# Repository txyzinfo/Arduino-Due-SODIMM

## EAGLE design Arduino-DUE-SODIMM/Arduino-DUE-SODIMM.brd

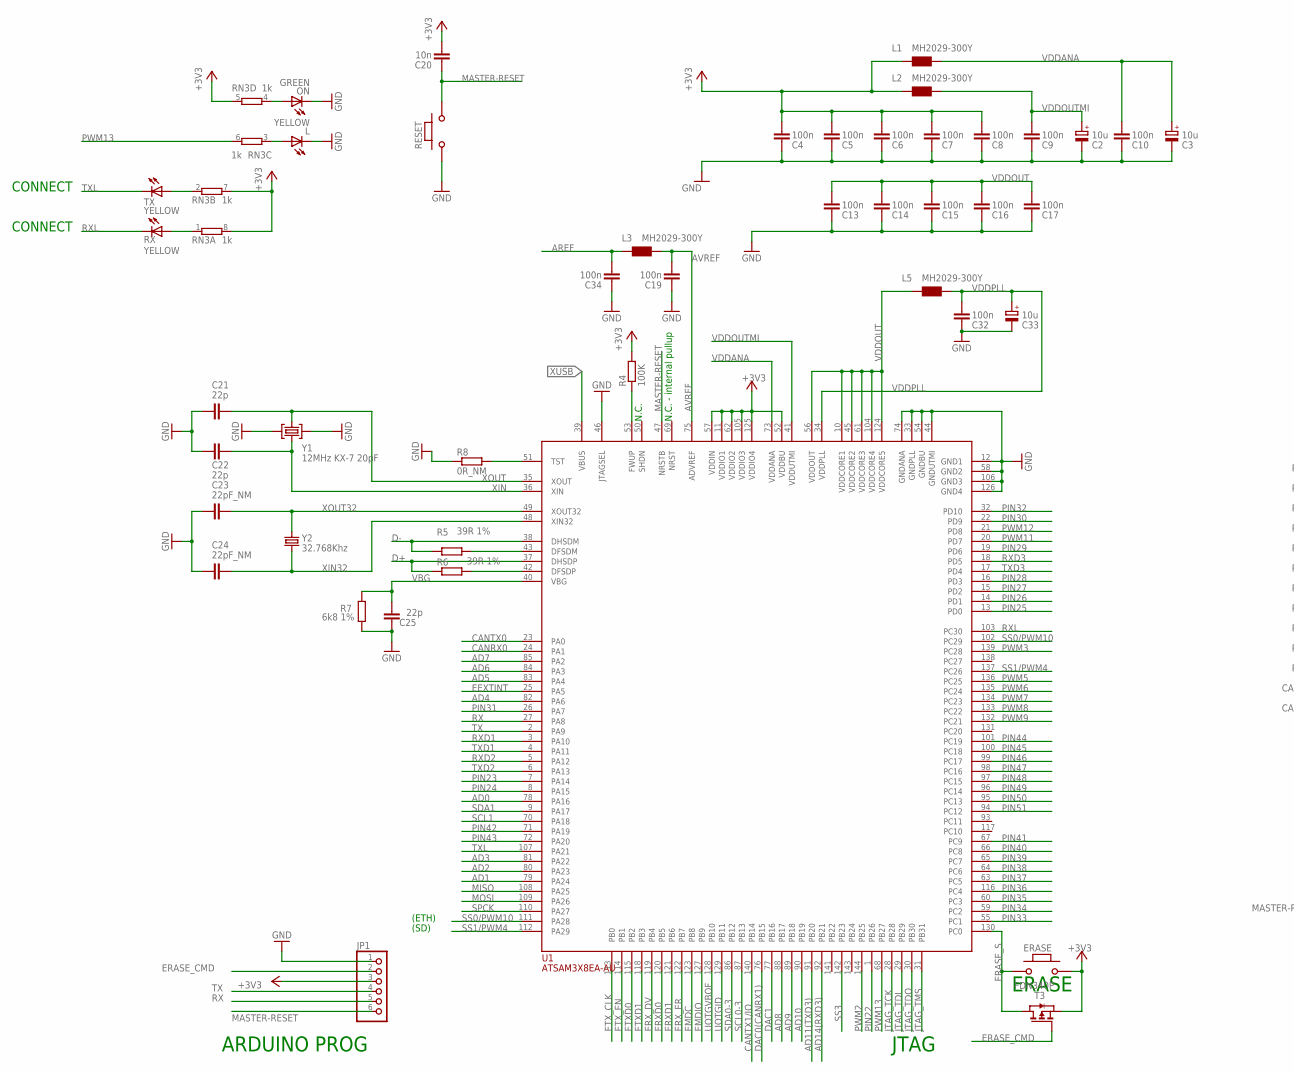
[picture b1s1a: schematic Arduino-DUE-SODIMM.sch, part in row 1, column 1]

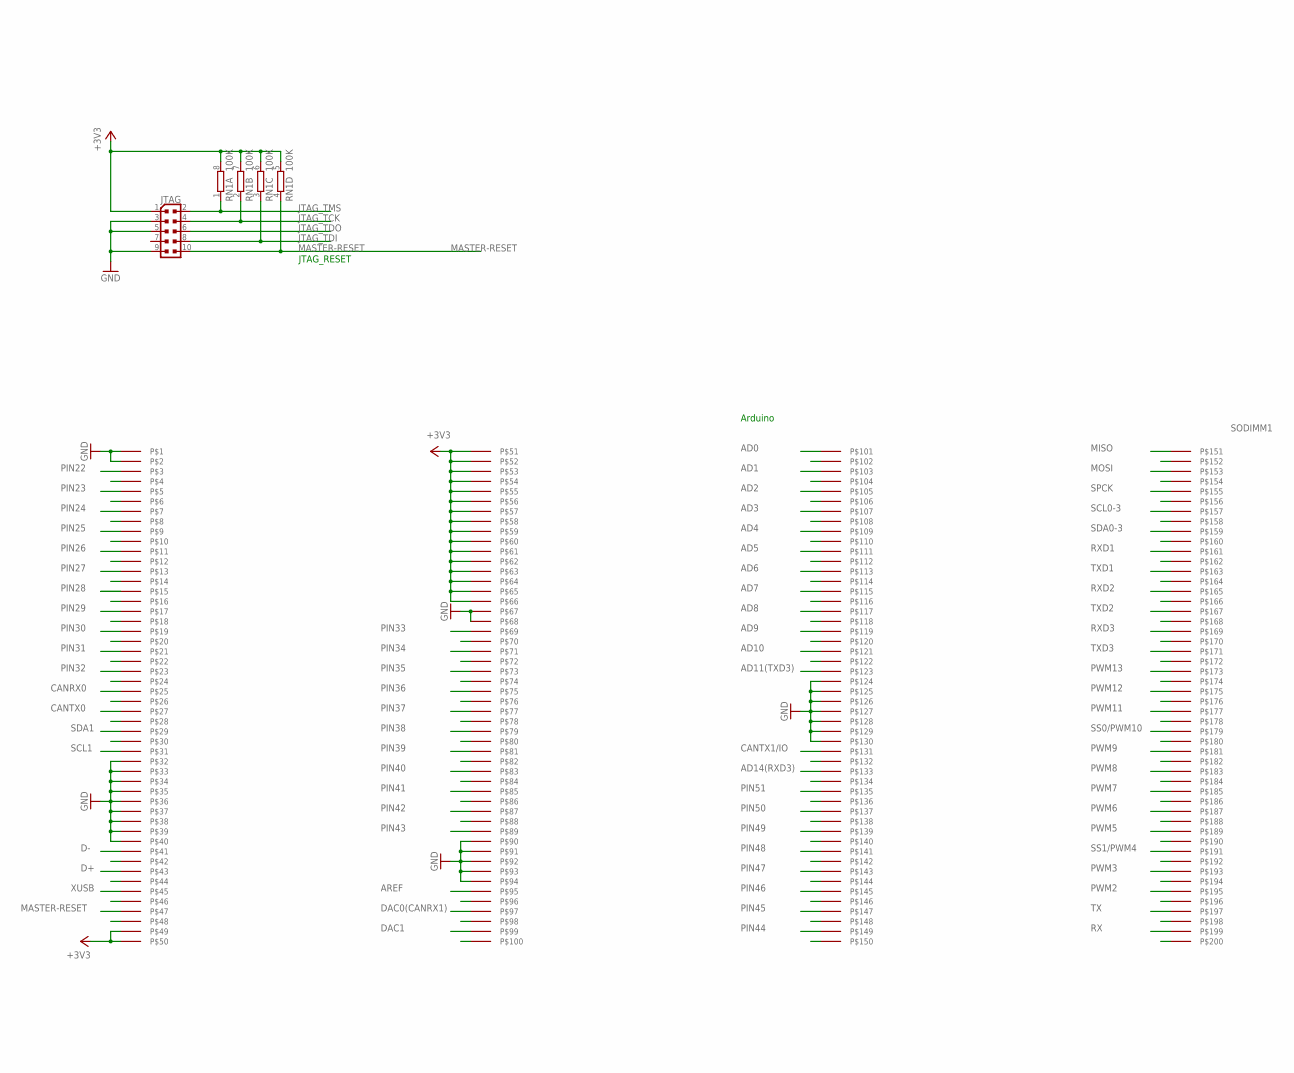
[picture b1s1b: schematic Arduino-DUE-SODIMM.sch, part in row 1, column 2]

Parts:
C2, C3, C33: 10u; SMC_B
C4, C5, C6, C7, C8, C9, C10, C13, C14, C15, C16, C17, C19, C32, C34: 100n; C0402
C20: 10n; C0402
C21, C22, C25: 22p; C0402
C23, C24: 22pF_NM; C0402
ERASE: MYSMD_PB157; SMD_157SW
JP1: PINHD-1X6CB; 1X06-CLEANBIG
JTAG: PINHEAD_PINHD-2X5PASSO127; PINHEAD_2X05_127
L: YELLOW; CHIP-LED0805
L1, L2, L3, L5: MH2029-300Y; 0805
ON: GREEN; CHIP-LED0805
R4: 100K; R0402
R5, R6: 39R 1%; R0402
R7: 6k8 1%; R0603-ROUND
R8: 0R_NM; R0402
RESET: MYSMD_PB157; SMD_157SW
RN1: 100K; CAT16
RN3: 1k; CAY16
RX: YELLOW; CHIP-LED0805
SODIMM1: SODIMM_BOARDLARGE; SODIMM-BOARD-67.6X50
T3: FDN340P; SOT-23
TX: YELLOW; CHIP-LED0805
U1: ATSAM3X8EA-AU; LQFP144
Y1: 12MHz KX-7 20pF; CRYSTAL-3.2-2.5
Y2: 32.768Khz; RESONATOR_EPSON_FC_145

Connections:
+3V3: C4.2, C5.2, C6.2, C7.2, C8.2, C20.2, ERASE.1, JP1.3, JTAG.1, L1.1, L2.1, R4.2, RN1.5 (2), RN1.6 (2), RN1.7 (2), RN1.8 (2), RN3.5 (2), RN3.7 (2), RN3.8 (2), SODIMM1.49, SODIMM1.50, SODIMM1.51, SODIMM1.52, SODIMM1.53, SODIMM1.54, SODIMM1.55, SODIMM1.56, SODIMM1.57, SODIMM1.58, SODIMM1.59, SODIMM1.60, SODIMM1.61, SODIMM1.62, SODIMM1.63, SODIMM1.64, SODIMM1.65, SODIMM1.66, T3.2 (S), U1.11 (VDDIO1), U1.52 (VDDBU), U1.57 (VDDIN), U1.62 (VDDIO2), U1.105 (VDDIO3), U1.125 (VDDIO4)
AD0: SODIMM1.101, U1.78 (PA16)
AD1: SODIMM1.103, U1.79 (PA24)
AD2: SODIMM1.105, U1.80 (PA23)
AD3: SODIMM1.107, U1.81 (PA22)
AD4: SODIMM1.109, U1.82 (PA6)
AD5: SODIMM1.111, U1.83 (PA4)
AD6: SODIMM1.113, U1.84 (PA3)
AD7: SODIMM1.115, U1.85 (PA2)
AD8: SODIMM1.117, U1.88 (PB17)
AD9: SODIMM1.119, U1.89 (PB18)
AD10: SODIMM1.121, U1.90 (PB19)
AD11(TXD3): SODIMM1.123, U1.91 (PB20)
AD14(RXD3): SODIMM1.133, U1.92 (PB21)
AREF: C34.2, L3.1, SODIMM1.95
AVREF: C19.2, L3.2, U1.75 (ADVREF)
CANRX0: SODIMM1.25, U1.24 (PA1)
CANTX0: SODIMM1.27, U1.23 (PA0)
CANTX1/IO: SODIMM1.131, U1.140 (PB14)
D+: R6.1, SODIMM1.43, U1.37 (DHSDP)
D-: R5.1, SODIMM1.41, U1.38 (DHSDM)
DAC0(CANRX1): SODIMM1.97, U1.76 (PB15)
DAC1: SODIMM1.99, U1.77 (PB16)
EEXTINT: U1.25 (PA5)
EMDC: U1.123 (PB8)
EMDIO: U1.127 (PB9)
ERASE_CMD: JP1.2, T3.3 (G)
ERASE_S: ERASE.2, T3.1 (D), U1.130 (PC0)
ERXD0: U1.120 (PB5)
ERXD1: U1.121 (PB6)
ERX_DV: U1.119 (PB4)
ERX_ER: U1.122 (PB7)
ETXD0: U1.115 (PB2)
ETXD1: U1.118 (PB3)
ETX_CLK: U1.113 (PB0)
ETX_EN: U1.114 (PB1)
GND: C2.-, C3.-, C4.1, C5.1, C6.1, C7.1, C8.1, C9.1, C10.1, C13.1, C14.1, C15.1, C16.1, C17.1, C19.1, C21.2, C22.2, C23.2, C24.2, C25.2, C32.1, C33.-, C34.1, JP1.1, JTAG.3, JTAG.5, JTAG.9, L.C, ON.C, R7.1, R8.1, RESET.2, SODIMM1.1, SODIMM1.2, SODIMM1.4, SODIMM1.6, SODIMM1.8, SODIMM1.10, SODIMM1.12, SODIMM1.14, SODIMM1.16, SODIMM1.18, SODIMM1.20, SODIMM1.22, SODIMM1.24, SODIMM1.26, SODIMM1.28, SODIMM1.30, SODIMM1.32, SODIMM1.33, SODIMM1.34, SODIMM1.35, SODIMM1.36, SODIMM1.37, SODIMM1.38, SODIMM1.39, SODIMM1.40, SODIMM1.42, SODIMM1.44, SODIMM1.46, SODIMM1.48, SODIMM1.67, SODIMM1.68, SODIMM1.70, SODIMM1.72, SODIMM1.74, SODIMM1.76, SODIMM1.78, SODIMM1.80, SODIMM1.82, SODIMM1.84, SODIMM1.86, SODIMM1.88, SODIMM1.90, SODIMM1.91, SODIMM1.92, SODIMM1.93, SODIMM1.94, SODIMM1.96, SODIMM1.98, SODIMM1.100, SODIMM1.102, SODIMM1.106, SODIMM1.108, SODIMM1.110, SODIMM1.112, SODIMM1.114, SODIMM1.116, SODIMM1.118, SODIMM1.120, SODIMM1.122, SODIMM1.124, SODIMM1.125, SODIMM1.126, SODIMM1.127, SODIMM1.128, SODIMM1.129, SODIMM1.130, SODIMM1.132, SODIMM1.134, SODIMM1.136, SODIMM1.138, SODIMM1.140, SODIMM1.142, SODIMM1.144, SODIMM1.146, SODIMM1.148, SODIMM1.150, SODIMM1.152, SODIMM1.154, SODIMM1.156, SODIMM1.158, SODIMM1.160, SODIMM1.162, SODIMM1.164, SODIMM1.166, SODIMM1.168, SODIMM1.170, SODIMM1.172, SODIMM1.174, SODIMM1.176, SODIMM1.178, SODIMM1.180, SODIMM1.182, SODIMM1.184, SODIMM1.186, SODIMM1.188, SODIMM1.190, SODIMM1.192, SODIMM1.194, SODIMM1.196, SODIMM1.198, SODIMM1.200, U1.12 (GND1), U1.33 (GNDPLL), U1.44 (GNDUTMI), U1.46 (JTAGSEL), U1.54 (GNDBU), U1.58 (GND2), U1.74 (GNDANA), U1.106 (GND3), U1.126 (GND4), Y1.2 (GND), Y1.4 (GND)
JTAG_TCK: JTAG.4, RN1.2 (1), U1.28 (PB28)
JTAG_TDI: JTAG.8, RN1.3 (1), U1.29 (PB29)
JTAG_TDO: JTAG.6, U1.30 (PB30)
JTAG_TMS: JTAG.2, RN1.1, U1.31 (PB31)
MASTER-RESET: C20.1, JP1.6, JTAG.10, RESET.1, RN1.4 (1), SODIMM1.47, U1.47 (NRSTB)
MISO: SODIMM1.151, U1.108 (PA25)
MOSI: SODIMM1.153, U1.109 (PA26)
unnamed: L.A, RN3.3 (1)
unnamed: ON.A, RN3.4 (1)
unnamed: R8.2, U1.51 (TST)
unnamed: R4.1, U1.53 (FWUP)
unnamed: R5.2, U1.43 (DFSDM)
unnamed: R6.2, U1.42 (DFSDP)
unnamed: RN3.1, RX.A
unnamed: RN3.2 (1), TX.A
PIN22: SODIMM1.3, U1.1 (PB26)
PIN23: SODIMM1.5, U1.7 (PA14)
PIN24: SODIMM1.7, U1.8 (PA15)
PIN25: SODIMM1.9, U1.13 (PD0)
PIN26: SODIMM1.11, U1.14 (PD1)
PIN27: SODIMM1.13, U1.15 (PD2)
PIN28: SODIMM1.15, U1.16 (PD3)
PIN29: SODIMM1.17, U1.19 (PD6)
PIN30: SODIMM1.19, U1.22 (PD9)
PIN31: SODIMM1.21, U1.26 (PA7)
PIN32: SODIMM1.23, U1.32 (PD10)
PIN33: SODIMM1.69, U1.55 (PC1)
PIN34: SODIMM1.71, U1.59 (PC2)
PIN35: SODIMM1.73, U1.60 (PC3)
PIN36: SODIMM1.75, U1.116 (PC4)
PIN37: SODIMM1.77, U1.63 (PC5)
PIN38: SODIMM1.79, U1.64 (PC6)
PIN39: SODIMM1.81, U1.65 (PC7)
PIN40: SODIMM1.83, U1.66 (PC8)
PIN41: SODIMM1.85, U1.67 (PC9)
PIN42: SODIMM1.87, U1.71 (PA19)
PIN43: SODIMM1.89, U1.72 (PA20)
PIN44: SODIMM1.149, U1.101 (PC19)
PIN45: SODIMM1.147, U1.100 (PC18)
PIN46: SODIMM1.145, U1.99 (PC17)
PIN47: SODIMM1.143, U1.98 (PC16)
PIN48: SODIMM1.141, U1.97 (PC15)
PIN49: SODIMM1.139, U1.96 (PC14)
PIN50: SODIMM1.137, U1.95 (PC13)
PIN51: SODIMM1.135, U1.94 (PC12)
PWM2: SODIMM1.195, U1.144 (PB25)
PWM3: SODIMM1.193, U1.139 (PC28)
PWM5: SODIMM1.189, U1.136 (PC25)
PWM6: SODIMM1.187, U1.135 (PC24)
PWM7: SODIMM1.185, U1.134 (PC23)
PWM8: SODIMM1.183, U1.133 (PC22)
PWM9: SODIMM1.181, U1.132 (PC21)
PWM11: SODIMM1.177, U1.20 (PD7)
PWM12: SODIMM1.175, U1.21 (PD8)
PWM13: RN3.6 (2), SODIMM1.173, U1.68 (PB27)
RX: JP1.5, SODIMM1.199, U1.27 (PA8)
RXD1: SODIMM1.161, U1.3 (PA10)
RXD2: SODIMM1.165, U1.5 (PA12)
RXD3: SODIMM1.169, U1.18 (PD5)
RXL: RX.C, U1.103 (PC30)
SCL0-3: SODIMM1.157, U1.87 (PB13)
SCL1: SODIMM1.31, U1.70 (PA18)
SDA0-3: SODIMM1.159, U1.86 (PB12)
SDA1: SODIMM1.29, U1.9 (PA17)
SPCK: SODIMM1.155, U1.110 (PA27)
SS0/PWM10: SODIMM1.179, U1.102 (PC29), U1.111 (PA28)
SS1/PWM4: SODIMM1.191, U1.112 (PA29), U1.137 (PC26)
SS3: U1.142 (PB23)
TX: JP1.4, SODIMM1.197, U1.2 (PA9)
TXD1: SODIMM1.163, U1.4 (PA11)
TXD2: SODIMM1.167, U1.6 (PA13)
TXD3: SODIMM1.171, U1.17 (PD4)
TXL: TX.C, U1.107 (PA21)
UOTGID: U1.129 (PB11)
UOTGVBOF: U1.128 (PB10)
VBG: C25.1, R7.2, U1.40 (VBG)
VDDANA: C3.+, C10.2, L1.2, U1.73 (VDDANA)
VDDOUT: C13.2, C14.2, C15.2, C16.2, C17.2, L5.1, U1.10 (VDDCORE1), U1.45 (VDDCORE2), U1.56 (VDDOUT), U1.61 (VDDCORE3), U1.104 (VDDCORE4), U1.124 (VDDCORE5)
VDDOUTMI: C2.+, C9.2, L2.2, U1.41 (VDDUTMI)
VDDPLL: C32.2, C33.+, L5.2, U1.34 (VDDPLL)
XIN: C22.1, U1.36 (XIN), Y1.1 (C1)
XIN32: C24.1, U1.48 (XIN32), Y2.P$2 (2)
XOUT: C21.1, U1.35 (XOUT), Y1.3 (C2)
XOUT32: C23.1, U1.49 (XOUT32), Y2.P$1 (1)
XUSB: SODIMM1.45, U1.39 (VBUS)

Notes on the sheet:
N.C.
JTAG
ERASE
CONNECT
(ETH)
(SD)
N.C. - internal pullup
ARDUINO PROG
JTAG_RESET
Arduino

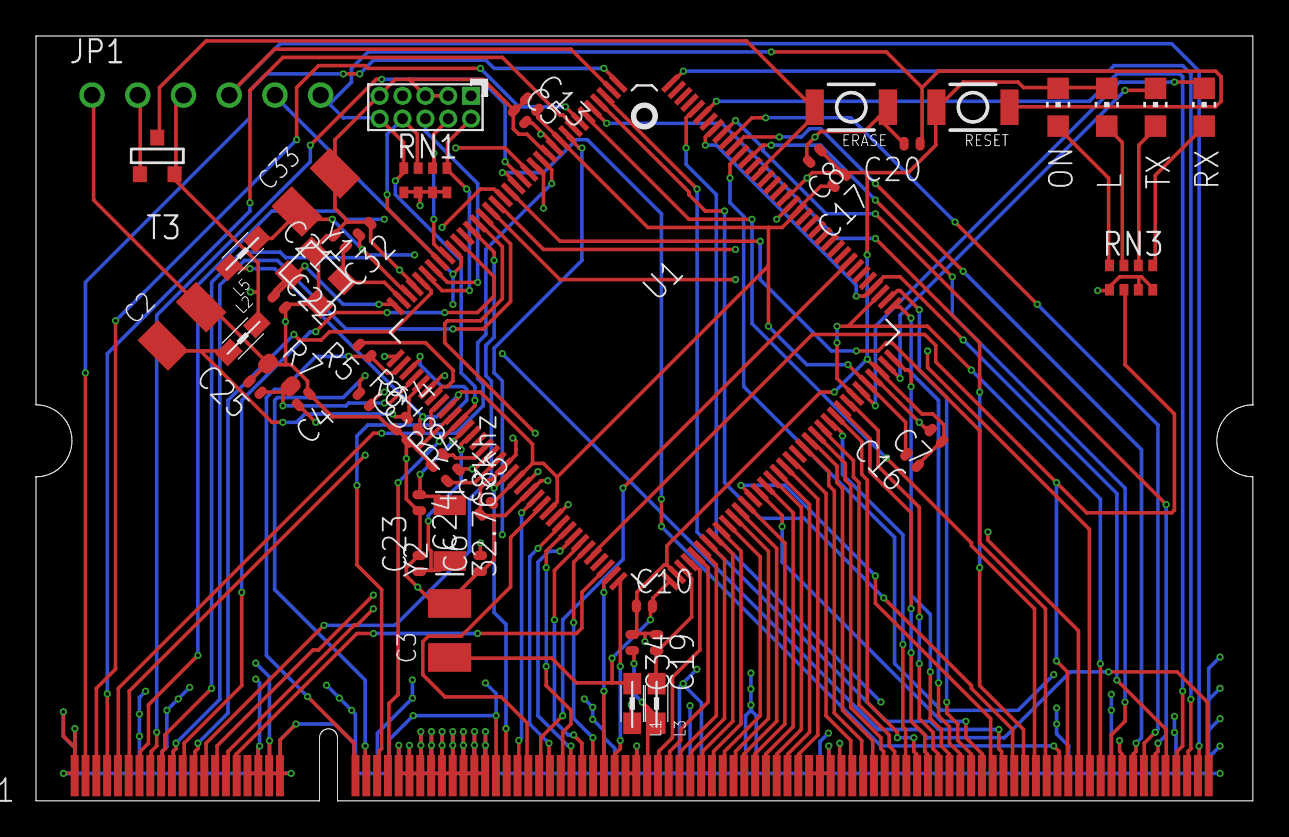
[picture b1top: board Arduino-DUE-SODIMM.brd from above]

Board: 4 copper layers, 67.6 x 42.5 mm, 48 parts (0 on the bottom side), 108 nets.

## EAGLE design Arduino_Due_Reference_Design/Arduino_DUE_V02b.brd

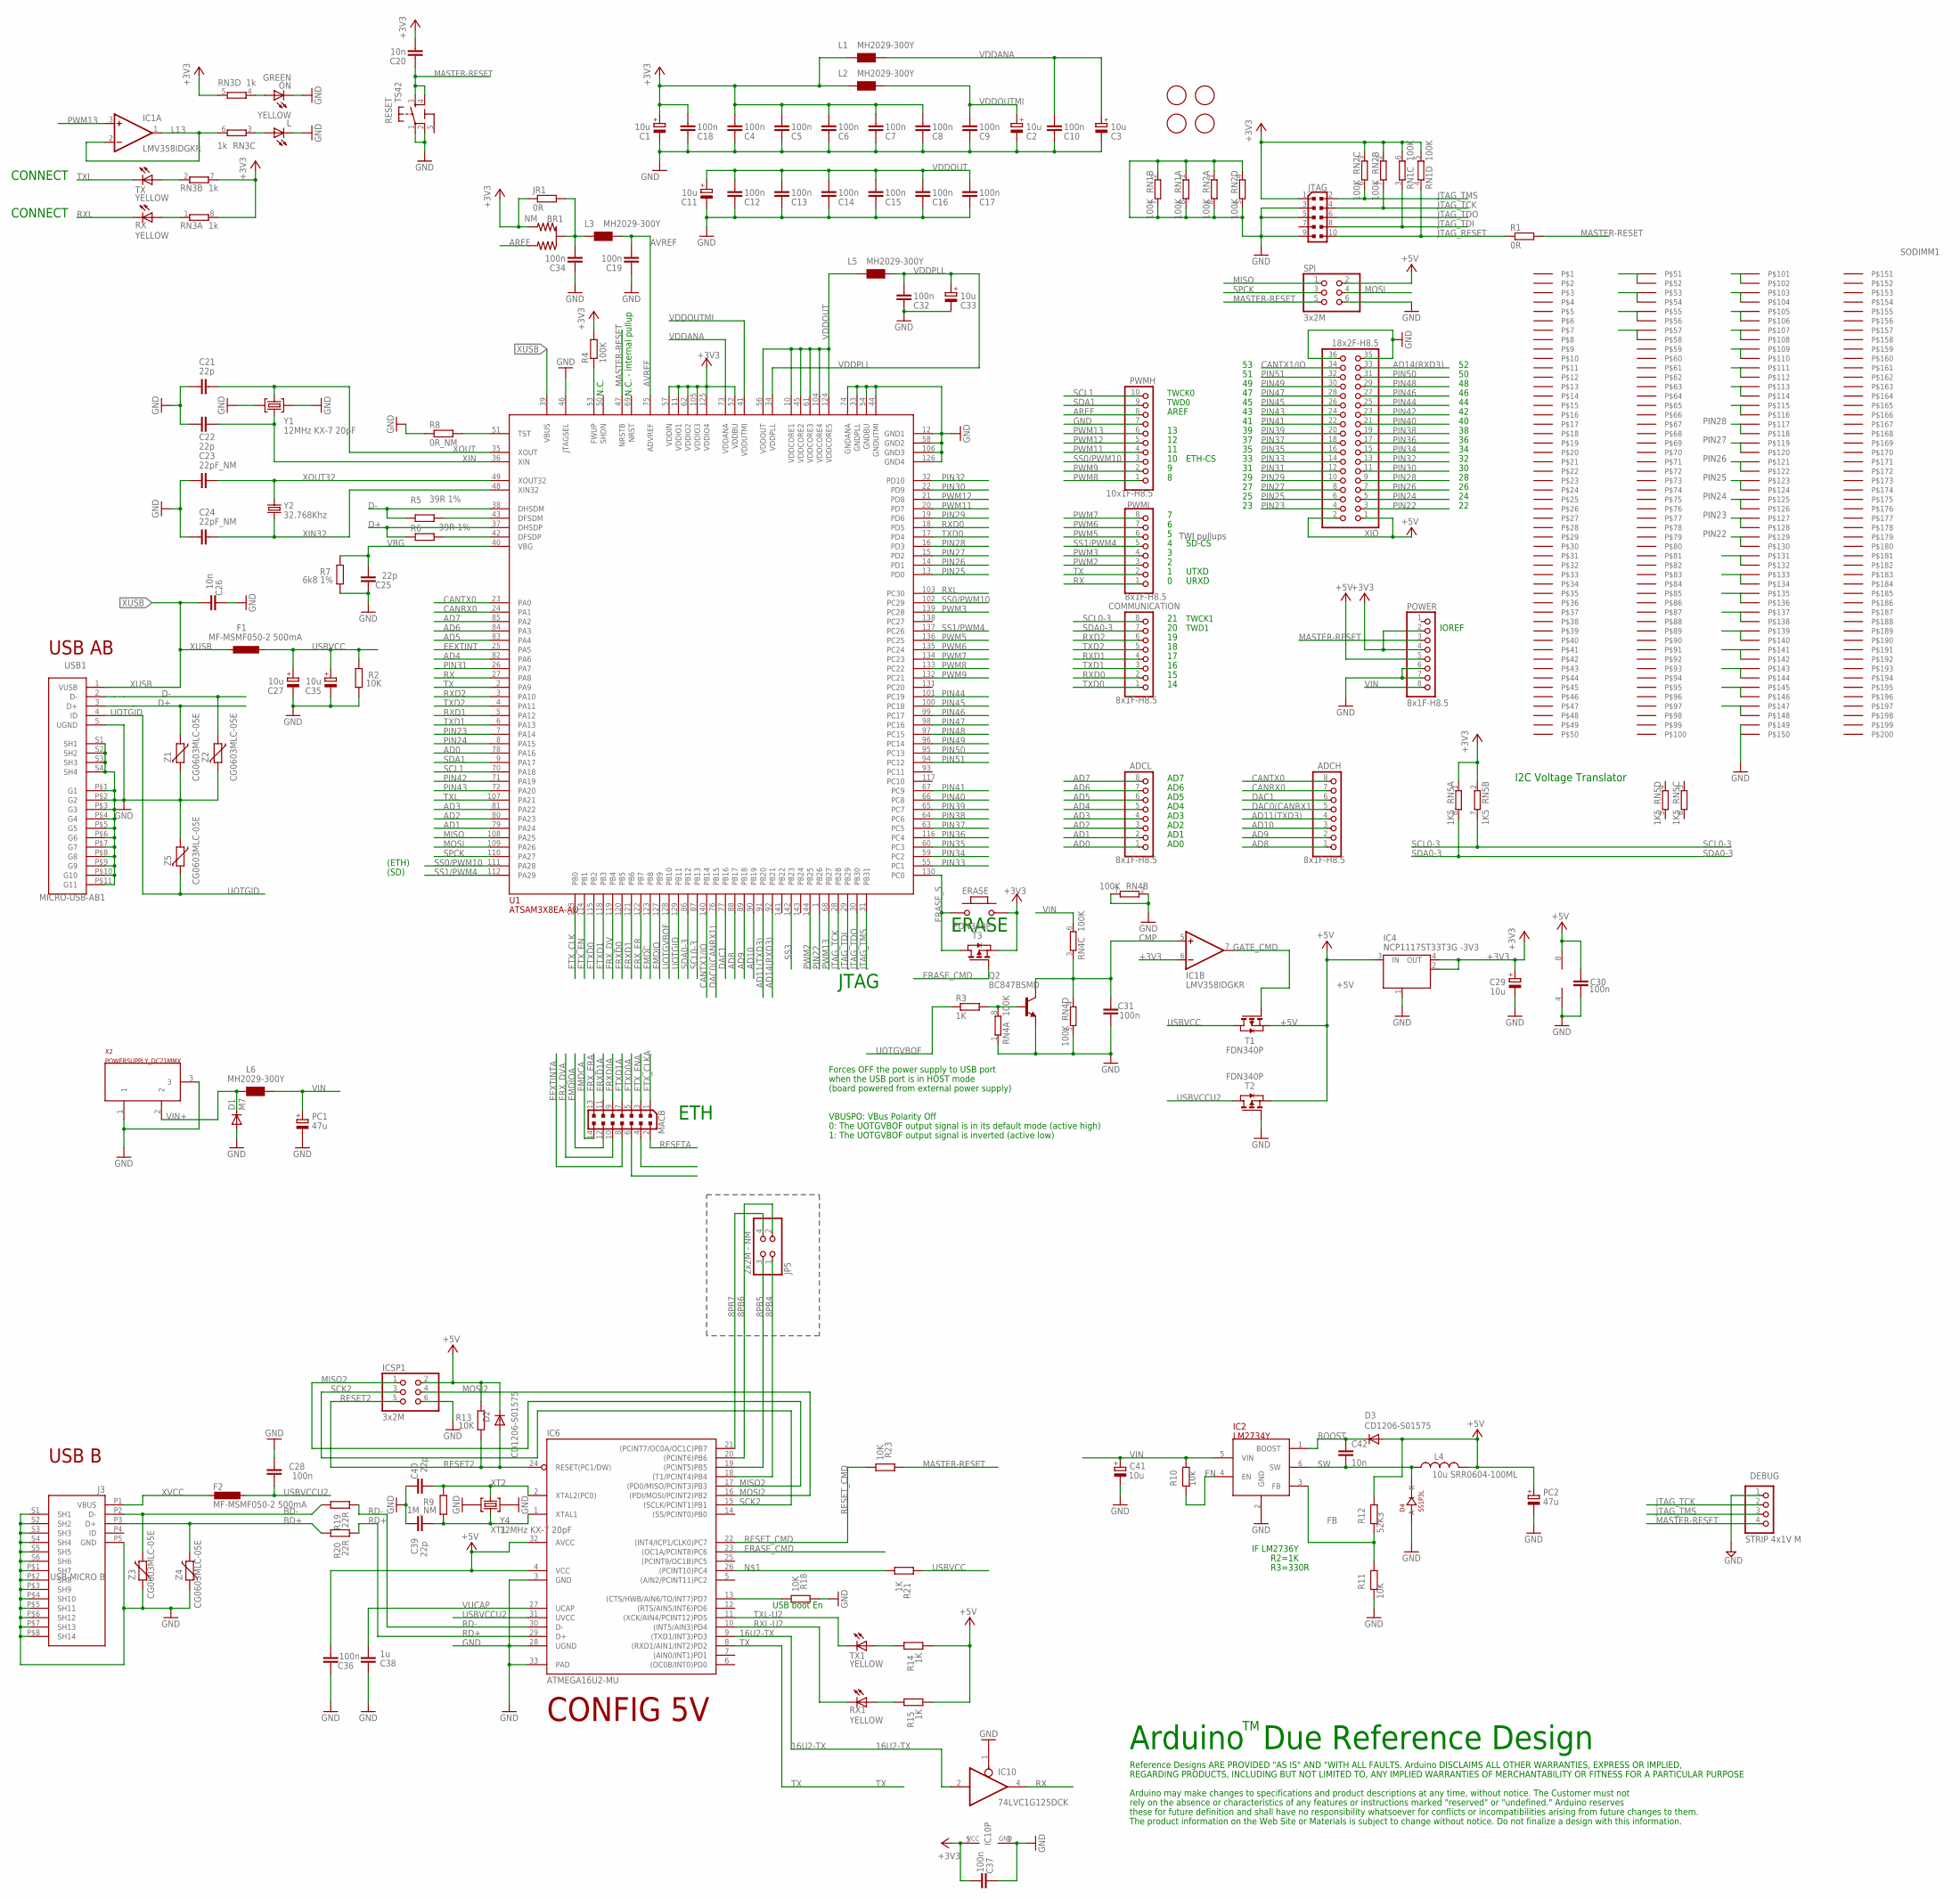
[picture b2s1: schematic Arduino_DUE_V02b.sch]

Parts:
ADCH: 8x1F-H8.5; 1X08
ADCL: 8x1F-H8.5; 1X08
BR1: NM; J0402
C1, C2, C3, C11, C27, C29, C33, C35, C41: 10u; SMC_B
C4, C5, C6, C7, C8, C9, C10, C12, C13, C14, C15, C16, C17, C18, C19, C28, C30, C31, C32, C34, C36, C37: 100n; C0402
C20, C26: 10n; C0402
C21, C22, C25, C39, C40: 22p; C0402
C23, C24: 22pF_NM; C0402
C38: 1u; C0402
C42: 10n; C0603-ROUND
COMMUNICATION: 8x1F-H8.5; 1X08
D1: M7; SMB
D2, D3: CD1206-S01575; MINIMELF
D4: SS1P3L; DO220AAL
DEBUG: STRIP 4x1V M; 1X04
ERASE: MYSMD_PB157; SMD_157SW
F1, F2: MF-MSMF050-2 500mA; L1812
FID1, FID2, FID3, FID4: FIDUCIALMOUNT; FIDUCIA-MOUNT
IC1: LMV358IDGKR; MSOP08
IC2: LM2734Y; SOT23-6
IC4: NCP1117ST33T3G -3V3; SOT223
IC6: ATMEGA16U2-MU; MLF32
IC10: 74LVC1G125DCK; SC70-5
ICSP1: 3x2M; 2X03
J3: USB-MICRO B; CON2_USB_MICRO_B_AT
JP5: 2x2M - NM; 2X02
JR1: 0R; R0402
JTAG: PINHEAD_PINHD-2X5PASSO127; PINHEAD_2X05_127
L: YELLOW; CHIP-LED0805
L1, L2, L3, L5, L6: MH2029-300Y; 0805
L4: 10u SRR0604-100ML; SRR0604
MACB: PINHEAD_PINHD-2X7PASSO127; PINHEAD_2X07_127
ON: GREEN; CHIP-LED0805
PC1, PC2: 47u; PANASONIC_D
POWER: 8x1F-H8.5; 1X08
PWMH: 10x1F-H8.5; 1X10
PWML: 8x1F-H8.5; 1X08
Q2: BC847BSMD; SOT23
R1: 0R; R0402
R2, R13, R18, R23: 10K; R0402
R3, R14, R15, R21: 1K; R0402
R4: 100K; R0402
R5, R6: 39R 1%; R0402
R7: 6k8 1%; R0603-ROUND
R8: 0R_NM; R0402
R9: 1M_NM; R0402
R10: 10k; R0402
R11: 10K; R0603-ROUND
R12: 52K3; R0603-ROUND
R19, R20: 22R; R0402
RESET: TS42
RN1, RN2, RN4: 100K; CAT16
RN3: 1k; CAY16
RN5: 1K5; CAT16
RX, RX1: YELLOW; CHIP-LED0805
SODIMM1: SODIMM_BOARDSMALL; SODIMM_BOARD_SMALLER-67.6X35
SPI: 3x2M; 2X03
T1, T2, T3: FDN340P; SOT-23
TX, TX1: YELLOW; CHIP-LED0805
U1: ATSAM3X8EA-AU; LQFP144
USB1: MICRO-USB-AB1; MCR-AB1-S-RA-SMT
X2: POWERSUPPLY_DC21MMX; POWERSUPPLY_DC-21MM
XIO: 18x2F-H8.5; 2X18
Y1, Y4: 12MHz KX-7 20pF; CRYSTAL-3.2-2.5
Y2: 32.768Khz; RESONATOR_EPSON_FC_145
Z1, Z2, Z3, Z4, Z5: CG0603MLC-05E; CT/CN0603

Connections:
5-GND: RESET.5 (5-GND)
8PB4: IC6.18 ((T1/PCINT4)PB4), JP5.1
8PB5: IC6.19 ((PCINT5)PB5), JP5.3
8PB6: IC6.20 ((PCINT6)PB6), JP5.2
8PB7: IC6.21 ((PCINT7/OC0A/OC1C)PB7), JP5.4
16U2-TX: IC6.9 ((TXD1/INT3)PD3), IC10.2 (I)
+3V3: BR1.3 (2), C1.+, C4.2, C5.2, C6.2, C7.2, C8.2, C18.2, C20.2, C29.+, C37.1, ERASE.1, IC1.6 (-IN), IC4.2 (OUT), IC4.4 (OUT), IC10.5 (VCC), JR1.1, JTAG.1, L1.1, L2.1, POWER.2, POWER.4, R4.2, RN1.5 (2), RN1.6 (2), RN2.2 (1), RN2.3 (1), RN3.5 (2), RN3.7 (2), RN3.8 (2), RN5.1, RN5.2 (1), T3.2 (S), U1.11 (VDDIO1), U1.52 (VDDBU), U1.57 (VDDIN), U1.62 (VDDIO2), U1.105 (VDDIO3), U1.125 (VDDIO4)
+5V: C30.2, C36.1, D2.C, D3.A, IC1.8 (V+), IC4.3 (IN), IC6.4 (VCC), IC6.32 (AVCC), ICSP1.2, L4.P$2 (2), PC2.+, POWER.5, R12.1, R13.2, R14.1, R15.1, SPI.2, T1.2 (S), T2.2 (S), XIO.1, XIO.2
AD0: ADCL.1, U1.78 (PA16)
AD1: ADCL.2, U1.79 (PA24)
AD2: ADCL.3, U1.80 (PA23)
AD3: ADCL.4, U1.81 (PA22)
AD4: ADCL.5, U1.82 (PA6)
AD5: ADCL.6, U1.83 (PA4)
AD6: ADCL.7, U1.84 (PA3)
AD7: ADCL.8, U1.85 (PA2)
AD8: ADCH.1, U1.88 (PB17)
AD9: ADCH.2, U1.89 (PB18)
AD10: ADCH.3, U1.90 (PB19)
AD11(TXD3): ADCH.4, U1.91 (PB20)
AD14(RXD3): SODIMM1.53, SODIMM1.54, U1.92 (PB21), XIO.33
AREF: BR1.1, PWMH.8
AVREF: C19.2, L3.2, U1.75 (ADVREF)
AVREFL: BR1.2 (C), C34.2, JR1.2, L3.1
BD+: J3.P3 (D+), R20.2, Z4.2
BD-: J3.P2 (D-), R19.2, Z3.2
BOOST: C42.1, D3.C, IC2.1 (BOOST)
CANRX0: ADCH.7, U1.24 (PA1)
CANTX0: ADCH.8, U1.23 (PA0)
CANTX1/IO: SODIMM1.51, SODIMM1.52, U1.140 (PB14), XIO.34
CMP: C31.2, IC1.5 (+IN), Q2.3 (C), RN4.3 (1), RN4.4 (1)
D+: R6.1, U1.37 (DHSDP), USB1.3 (D+), Z1.1
D-: R5.1, U1.38 (DHSDM), USB1.2 (D-), Z2.1
DAC0(CANRX1): ADCH.5, U1.76 (PB15)
DAC1: ADCH.6, U1.77 (PB16)
DTR: IC6.13 ((CTS/HWB/AIN6/TO/INT7)PD7), R18.1
EEXTINT: U1.25 (PA5)
EEXTINTA: MACB.8
EMDC: U1.123 (PB8)
EMDCA: MACB.14
EMDIO: U1.127 (PB9)
EMDIOA: MACB.12 (13)
EN: IC2.4 (EN), R10.2
ERASE_CMD: IC6.23 ((OC1A/PCINT8)PC6), T3.3 (G)
ERASE_S: ERASE.2, T3.1 (D), U1.130 (PC0)
ERXD0: U1.120 (PB5)
ERXD0A: MACB.9
ERXD1: U1.121 (PB6)
ERXD1A: MACB.11
ERX_DV: U1.119 (PB4)
ERX_DVA: MACB.10
ERX_ER: U1.122 (PB7)
ERX_ERA: MACB.13 (12)
ETXD0: U1.115 (PB2)
ETXD0A: MACB.5
ETXD1: U1.118 (PB3)
ETXD1A: MACB.7
ETX_CLK: U1.113 (PB0)
ETX_CLKA: MACB.1
ETX_EN: U1.114 (PB1)
ETX_ENA: MACB.3
FB: IC2.3 (FB), R11.1, R12.2
GATE_CMD: IC1.7 (OUT), T1.3 (G)
GND: C1.-, C2.-, C3.-, C4.1, C5.1, C6.1, C7.1, C8.1, C9.1, C10.1, C11.-, C12.1, C13.1, C14.1, C15.1, C16.1, C17.1, C18.1, C19.1, C21.2, C22.2, C23.2, C24.2, C25.2, C26.2, C27.-, C28.2, C29.-, C30.1, C31.1, C32.1, C33.-, C34.1, C35.-, C36.2, C37.2, C38.2, C39.2, C40.2, C41.-, D1.A, D4.P$2 (A), DEBUG.1, IC1.4 (V-), IC2.2 (GND), IC4.1 (GND/ADJ), IC6.3 (GND), IC6.28 (UGND), IC6.33 (PAD), IC10.1 (OE), IC10.3 (GND), ICSP1.6, J3.P5 (GND), J3.P$1 (SH7), J3.P$2 (SH8), J3.P$3 (SH9), J3.P$4 (SH10), J3.P$5 (SH11), J3.P$6 (SH12), J3.P$7 (SH13), J3.P$8 (SH14), J3.S1 (SH1), J3.S2 (SH2), J3.S3 (SH3), J3.S4 (SH4), J3.S5 (SH5), J3.S6 (SH6), JTAG.3, JTAG.5, JTAG.9, L.C, ON.C, PC1.-, PC2.-, POWER.6, POWER.7, PWMH.7, Q2.2 (E), R2.1, R7.1, R8.1, R11.2, R18.2, RESET.1, RESET.2, RN1.1, RN1.2 (1), RN1.7 (2), RN1.8 (2), RN2.1, RN2.4 (1), RN2.5 (2), RN2.8 (2), RN4.1, RN4.2 (1), RN4.5 (2), RN4.7 (2), SODIMM1.149, SPI.6, T2.3 (G), U1.12 (GND1), U1.33 (GNDPLL), U1.44 (GNDUTMI), U1.46 (JTAGSEL), U1.54 (GNDBU), U1.58 (GND2), U1.74 (GNDANA), U1.106 (GND3), U1.126 (GND4), USB1.5 (UGND), USB1.P$1 (G1), USB1.P$2 (G2), USB1.P$3 (G3), USB1.P$4 (G4), USB1.P$5 (G5), USB1.P$6 (G6), USB1.P$7 (G7), USB1.P$8 (G8), USB1.P$9 (G9), USB1.P$10 (G10), USB1.P$11 (G11), USB1.S1 (SH1), USB1.S2 (SH2), USB1.S3 (SH3), USB1.S4 (SH4), X2.1, X2.3, XIO.35, XIO.36, Y1.2 (GND), Y1.4 (GND), Y4.2 (GND), Y4.4 (GND), Z1.2, Z2.2, Z3.1, Z4.1, Z5.1
JTAG_RESET: JTAG.10, R1.1, RN1.4 (1)
JTAG_TCK: DEBUG.2, JTAG.4, RN2.7 (2), U1.28 (PB28)
JTAG_TDI: JTAG.8, RN1.3 (1), U1.29 (PB29)
JTAG_TDO: JTAG.6, U1.30 (PB30)
JTAG_TMS: DEBUG.3, JTAG.2, RN2.6 (2), U1.31 (PB31)
L13: IC1.1 (OUT), IC1.2 (-IN), RN3.6 (2)
MASTER-RESET: C20.1, DEBUG.4, POWER.3, R1.2, R23.2, RESET.3, RESET.4, SPI.5, U1.47 (NRSTB)
MISO: SPI.1, U1.108 (PA25)
MISO2: IC6.17 ((PD0/MISO/PCINT3)PB3), ICSP1.1
MOSI: SPI.4, U1.109 (PA26)
MOSI2: IC6.16 ((PDI/MOSI/PCINT2)PB2), ICSP1.4
unnamed: IC6.26 ((PCINT10)PC4), R21.1
unnamed: L.A, RN3.3 (1)
unnamed: ON.A, RN3.4 (1)
unnamed: R15.2, RX1.A
unnamed: R8.2, U1.51 (TST)
unnamed: Q2.1 (B), R3.2, RN4.8 (2)
unnamed: R4.1, U1.53 (FWUP)
unnamed: SODIMM1.147, SODIMM1.148
unnamed: R5.2, U1.43 (DFSDM)
unnamed: R6.2, U1.42 (DFSDP)
unnamed: SODIMM1.57, SODIMM1.58
unnamed: R14.2, TX1.A
unnamed: SODIMM1.145, SODIMM1.146
unnamed: SODIMM1.143, SODIMM1.144
unnamed: SODIMM1.141, SODIMM1.142
unnamed: SODIMM1.139, SODIMM1.140
unnamed: SODIMM1.137, SODIMM1.138
unnamed: SODIMM1.135, SODIMM1.136
unnamed: SODIMM1.133, SODIMM1.134
unnamed: SODIMM1.131, SODIMM1.132
unnamed: SODIMM1.113, SODIMM1.114
unnamed: SODIMM1.111, SODIMM1.112
unnamed: SODIMM1.109, SODIMM1.110
unnamed: SODIMM1.107, SODIMM1.108
unnamed: SODIMM1.105, SODIMM1.106
unnamed: SODIMM1.103, SODIMM1.104
unnamed: SODIMM1.101, SODIMM1.102
unnamed: RN3.1, RX.A
unnamed: RN3.2 (1), TX.A
PIN22: SODIMM1.129, SODIMM1.130, U1.1 (PB26), XIO.3
PIN23: SODIMM1.127, SODIMM1.128, U1.7 (PA14), XIO.4
PIN24: SODIMM1.125, SODIMM1.126, U1.8 (PA15), XIO.5
PIN25: SODIMM1.123, SODIMM1.124, U1.13 (PD0), XIO.6
PIN26: SODIMM1.121, SODIMM1.122, U1.14 (PD1), XIO.7
PIN27: SODIMM1.119, SODIMM1.120, U1.15 (PD2), XIO.8
PIN28: SODIMM1.115, SODIMM1.116, SODIMM1.117, SODIMM1.118, U1.16 (PD3), XIO.9
PIN29: U1.19 (PD6), XIO.10
PIN30: U1.22 (PD9), XIO.11
PIN31: U1.26 (PA7), XIO.12
PIN32: U1.32 (PD10), XIO.13
PIN33: U1.55 (PC1), XIO.14
PIN34: U1.59 (PC2), XIO.15
PIN35: U1.60 (PC3), XIO.16
PIN36: U1.116 (PC4), XIO.17
PIN37: U1.63 (PC5), XIO.18
PIN38: U1.64 (PC6), XIO.19
PIN39: U1.65 (PC7), XIO.20
PIN40: U1.66 (PC8), XIO.21
PIN41: U1.67 (PC9), XIO.22
PIN42: U1.71 (PA19), XIO.23
PIN43: U1.72 (PA20), XIO.24
PIN44: U1.101 (PC19), XIO.25
PIN45: U1.100 (PC18), XIO.26
PIN46: U1.99 (PC17), XIO.27
PIN47: U1.98 (PC16), XIO.28
PIN48: U1.97 (PC15), XIO.29
PIN49: U1.96 (PC14), XIO.30
PIN50: U1.95 (PC13), XIO.31
PIN51: SODIMM1.55, SODIMM1.56, U1.94 (PC12), XIO.32
PWM2: PWML.3, U1.144 (PB25)
PWM3: PWML.4, U1.139 (PC28)
PWM5: PWML.6, U1.136 (PC25)
PWM6: PWML.7, U1.135 (PC24)
PWM7: PWML.8, U1.134 (PC23)
PWM8: PWMH.1, U1.133 (PC22)
PWM9: PWMH.2, U1.132 (PC21)
PWM11: PWMH.4, U1.20 (PD7)
PWM12: PWMH.5, U1.21 (PD8)
PWM13: IC1.3 (+IN), PWMH.6, U1.68 (PB27)
RD+: IC6.29 (D+), R20.1
RD-: IC6.30 (D-), R19.1
RESET2: D2.A, IC6.24 (RESET(PC1/DW)), ICSP1.5, R13.1
RESETA: MACB.2
RESET_CMD: IC6.22 ((INT4/ICP1/CLK0)PC7), R23.1
RX: IC10.4 (O), PWML.1, U1.27 (PA8)
RXD0: COMMUNICATION.2, U1.18 (PD5)
RXD1: COMMUNICATION.4, U1.5 (PA12)
RXD2: COMMUNICATION.6, U1.3 (PA10)
RXL: RX.C, U1.103 (PC30)
RXL-U2: IC6.10 ((INT5/AIN3)PD4), RX1.C
SCK2: IC6.15 ((SCLK/PCINT1)PB1), ICSP1.3
SCL0-3: COMMUNICATION.8, RN5.7 (2), U1.87 (PB13)
SCL1: PWMH.10, U1.70 (PA18)
SDA0-3: COMMUNICATION.7, RN5.8 (2), U1.86 (PB12)
SDA1: PWMH.9, U1.9 (PA17)
SPCK: SPI.3, U1.110 (PA27)
SS0/PWM10: PWMH.3, U1.102 (PC29), U1.111 (PA28)
SS1/PWM4: PWML.5, U1.112 (PA29), U1.137 (PC26)
SS3: U1.142 (PB23)
SW: C42.2, D4.P$1 (K), IC2.6 (SW), L4.P$1 (1)
TX: IC6.8 ((RXD1/AIN1/INT2)PD2), PWML.2, U1.2 (PA9)
TXD0: COMMUNICATION.1, U1.17 (PD4)
TXD1: COMMUNICATION.3, U1.6 (PA13)
TXD2: COMMUNICATION.5, U1.4 (PA11)
TXL: TX.C, U1.107 (PA21)
TXL-U2: IC6.11 ((XCK/AIN4/PCINT12)PD5), TX1.C
UOTGID: U1.129 (PB11), USB1.4 (ID), Z5.2
UOTGVBOF: R3.1, U1.128 (PB10)
USBVCC: C27.+, C35.+, F1.1, R2.2, R21.2, T1.1 (D)
USBVCCU2: C28.1, F2.1, IC6.31 (UVCC), T2.1 (D)
VBG: C25.1, R7.2, U1.40 (VBG)
VDDANA: C3.+, C10.2, L1.2, U1.73 (VDDANA)
VDDOUT: C11.+, C12.2, C13.2, C14.2, C15.2, C16.2, C17.2, L5.1, U1.10 (VDDCORE1), U1.45 (VDDCORE2), U1.56 (VDDOUT), U1.61 (VDDCORE3), U1.104 (VDDCORE4), U1.124 (VDDCORE5)
VDDOUTMI: C2.+, C9.2, L2.2, U1.41 (VDDUTMI)
VDDPLL: C32.2, C33.+, L5.2, U1.34 (VDDPLL)
VIN: C41.+, IC2.5 (VIN), L6.1, PC1.+, POWER.8, R10.1, RN4.6 (2)
VIN+: D1.C, L6.2, X2.2
VUCAP: C38.1, IC6.27 (UCAP)
XIN: C22.1, U1.36 (XIN), Y1.1 (C1)
XIN32: C24.1, U1.48 (XIN32), Y2.P$2 (2)
XOUT: C21.1, U1.35 (XOUT), Y1.3 (C2)
XOUT32: C23.1, U1.49 (XOUT32), Y2.P$1 (1)
XT1: C39.1, IC6.1 (XTAL1), R9.1, Y4.1 (C1)
XT2: C40.1, IC6.2 (XTAL2(PC0)), R9.2, Y4.3 (C2)
XUSB: C26.1, F1.2, U1.39 (VBUS), USB1.1 (VUSB)
XVCC: F2.2, J3.P1 (VBUS)

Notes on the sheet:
TWI pullups
TWCK1
TWD1
IOREF
TWCK0
TWD0
AD1
AD2
AD3
AD4
AD5
AD6
AD0
USB AB
AREF
AD7
SD-CS
Forces OFF the power supply to USB port
when the USB port is in HOST mode
(board powered from external power supply)
N.C.
JTAG
ERASE
CONNECT
VBUSPO: VBus Polarity Off
0: The UOTGVBOF output signal is in its default mode (active high)
1: The UOTGVBOF output signal is inverted (active low)
ETH
UTXD
URXD
(ETH)
(SD)
ETH-CS
I2C Voltage Translator
USB boot En
IF LM2736Y
R2=1K
R3=330R
CONFIG 5V
USB B

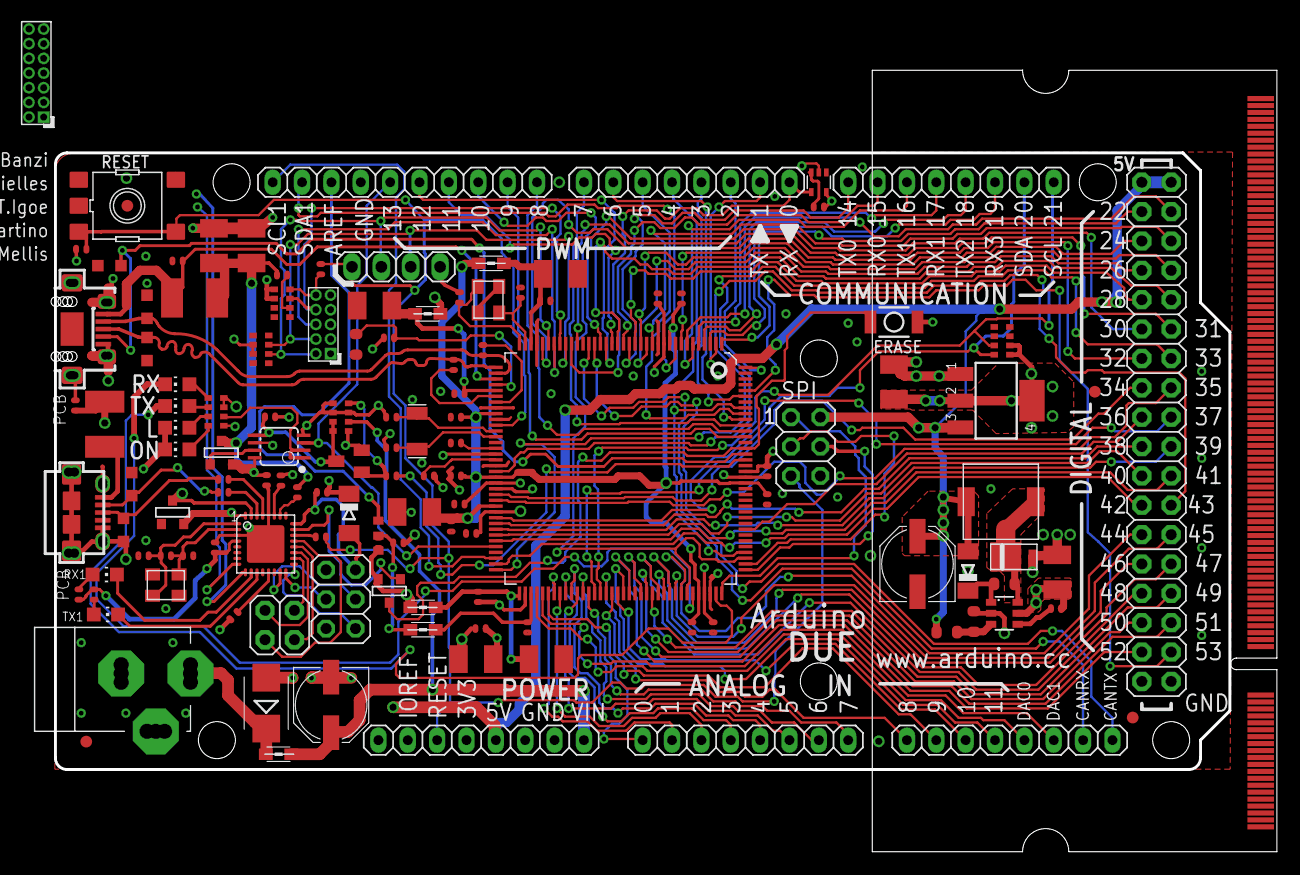
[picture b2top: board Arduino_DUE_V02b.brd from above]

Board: 4 copper layers, 105.7 x 67.6 mm, 130 parts (0 on the bottom side), 166 nets.

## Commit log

2016-11-30 :tada: Added .gitattributes & .gitignore files
2016-11-30 Arduino DUE in SODIMM
    Eagle Cad files
